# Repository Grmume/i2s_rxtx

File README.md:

# i2s_rxtx
Receiver and and (active) transmitter for I2S over ethernet cables.

Receiver for the 4 channels of digital audio (i2s) which can be transmitted using ethernet cables (>=Cat5).
Has a pin header to choose which channel is send to the i2s output, which can then be directed to an amp.
Contains an active transmitter to transmit all channels further to the next receiver.

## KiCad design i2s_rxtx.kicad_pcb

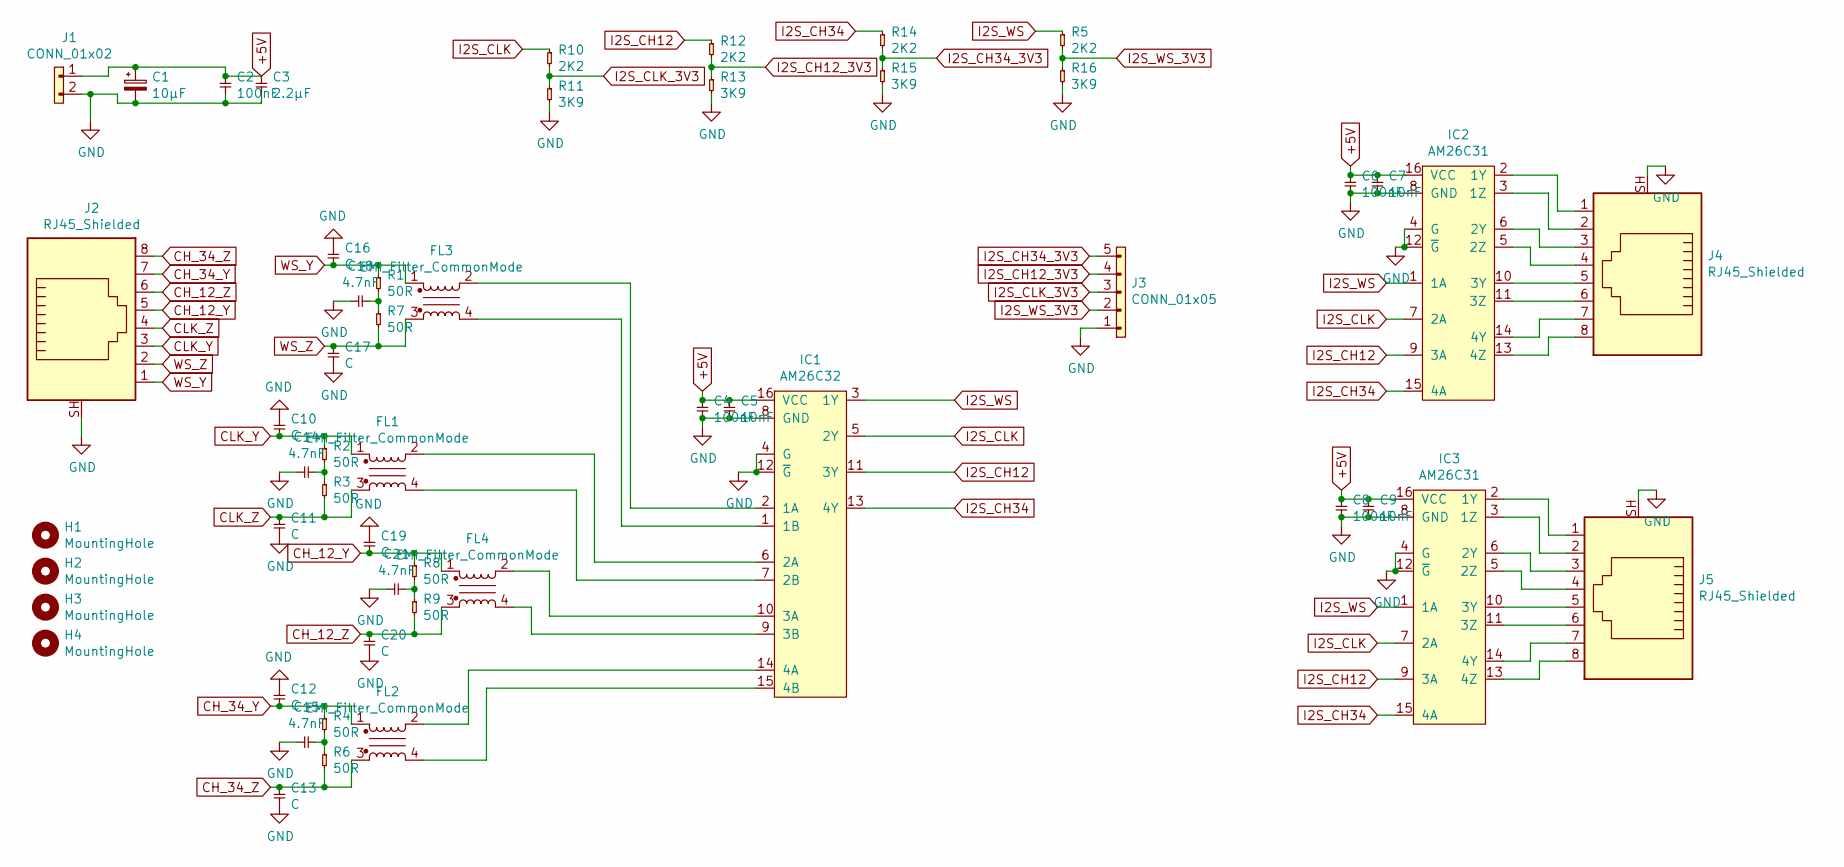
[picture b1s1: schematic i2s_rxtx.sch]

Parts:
C1: 10µF; CP_Elec_6.3x5.4
C2, C4, C6, C8: 100nF; C_0805_2012Metric_Pad1.15x1.40mm_HandSolder
C3: 2.2µF; C_0805_2012Metric_Pad1.15x1.40mm_HandSolder
C5, C7, C9: 10nF; C_0805_2012Metric_Pad1.15x1.40mm_HandSolder
C10, C11, C12, C13, C16, C17, C19, C20: C; C_0805_2012Metric_Pad1.15x1.40mm_HandSolder
C14, C15, C18, C21: 4.7nF; C_0805_2012Metric_Pad1.15x1.40mm_HandSolder
FL1, FL2, FL3, FL4: EMI_Filter_CommonMode; B82789_PinSwap
H1, H2, H3, H4: MountingHole; MountingHole_3.2mm_M3_Pad
IC1: AM26C32; SOIC-16; Farnell 1121592
IC2, IC3: AM26C31; SOIC-16; Farnell 4975637
J1: CONN_01x02; PinHeader_1x02_P2.00mm_Vertical
J2, J4, J5: RJ45_Shielded; RJ45_Weidmueller
J3: CONN_01x05; PinHeader_1x05_P2.00mm_Vertical
R1, R2, R3, R4, R6, R7, R8, R9: 50R; R_0805_2012Metric_Pad1.15x1.40mm_HandSolder
R5, R10, R12, R14: 2K2; R_0805_2012Metric_Pad1.15x1.40mm_HandSolder
R11, R13, R15, R16: 3K9; R_0805_2012Metric_Pad1.15x1.40mm_HandSolder

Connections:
+5V: C1.1, C2.1, C3.1, C4.1, C5.1, C6.1, C7.1, C8.1, C9.1, IC1.16 (VCC), IC2.16 (VCC), IC3.16 (VCC), J1.1
CH_12_Y: C19.2, FL4.1, J2.5, R8.1
CH_12_Z: C20.1, FL4.3, J2.6, R9.2
CH_34_Y: C12.2, FL2.1, J2.7, R4.1
CH_34_Z: C13.1, FL2.3, J2.8, R6.2
CLK_Y: C10.2, FL1.1, J2.3, R2.1
CLK_Z: C11.1, FL1.3, J2.4, R3.2
GND: C1.2, C2.2, C3.2, C4.2, C5.2, C6.2, C7.2, C8.2, C9.2, C10.1, C11.2, C12.1, C13.2, C14.1, C15.1, C16.1, C17.2, C18.1, C19.1, C20.2, C21.1, IC1.4 (G), IC1.8 (GND), IC1.12 (~G), IC2.4 (G), IC2.8 (GND), IC2.12 (~G), IC3.4 (G), IC3.8 (GND), IC3.12 (~G), J1.2, J2.SH, J3.1, J4.SH, J5.SH, R11.2, R13.2, R15.2, R16.2
I2S_CH12: IC1.11 (3Y), IC2.9 (3A), IC3.9 (3A), R12.1
I2S_CH12_3V3: J3.4, R12.2, R13.1
I2S_CH34: IC1.13 (4Y), IC2.15 (4A), IC3.15 (4A), R14.1
I2S_CH34_3V3: J3.5, R14.2, R15.1
I2S_CLK: IC1.5 (2Y), IC2.7 (2A), IC3.7 (2A), R10.1
I2S_CLK_3V3: J3.3, R10.2, R11.1
I2S_WS: IC1.3 (1Y), IC2.1 (1A), IC3.1 (1A), R5.1
I2S_WS_3V3: J3.2, R5.2, R16.1
unnamed: C14.2, R2.2, R3.1
unnamed: C15.2, R4.2, R6.1
unnamed: C18.2, R1.2, R7.1
unnamed: C21.2, R8.2, R9.1
unnamed: FL1.2, IC1.6 (2A)
unnamed: FL1.4, IC1.7 (2B)
unnamed: FL2.2, IC1.14 (4A)
unnamed: FL2.4, IC1.15 (4B)
unnamed: FL3.2, IC1.2 (1A)
unnamed: FL3.4, IC1.1 (1B)
unnamed: FL4.2, IC1.10 (3A)
unnamed: FL4.4, IC1.9 (3B)
unnamed: IC2.2 (1Y), J4.1
unnamed: IC2.3 (1Z), J4.2
unnamed: IC2.5 (2Z), J4.4
unnamed: IC2.6 (2Y), J4.3
unnamed: IC2.10 (3Y), J4.5
unnamed: IC2.11 (3Z), J4.6
unnamed: IC2.13 (4Z), J4.8
unnamed: IC2.14 (4Y), J4.7
unnamed: IC3.2 (1Y), J5.1
unnamed: IC3.3 (1Z), J5.2
unnamed: IC3.5 (2Z), J5.4
unnamed: IC3.6 (2Y), J5.3
unnamed: IC3.10 (3Y), J5.5
unnamed: IC3.11 (3Z), J5.6
unnamed: IC3.13 (4Z), J5.8
unnamed: IC3.14 (4Y), J5.7
WS_Y: C16.2, FL3.1, J2.1, R1.1
WS_Z: C17.1, FL3.3, J2.2, R7.2

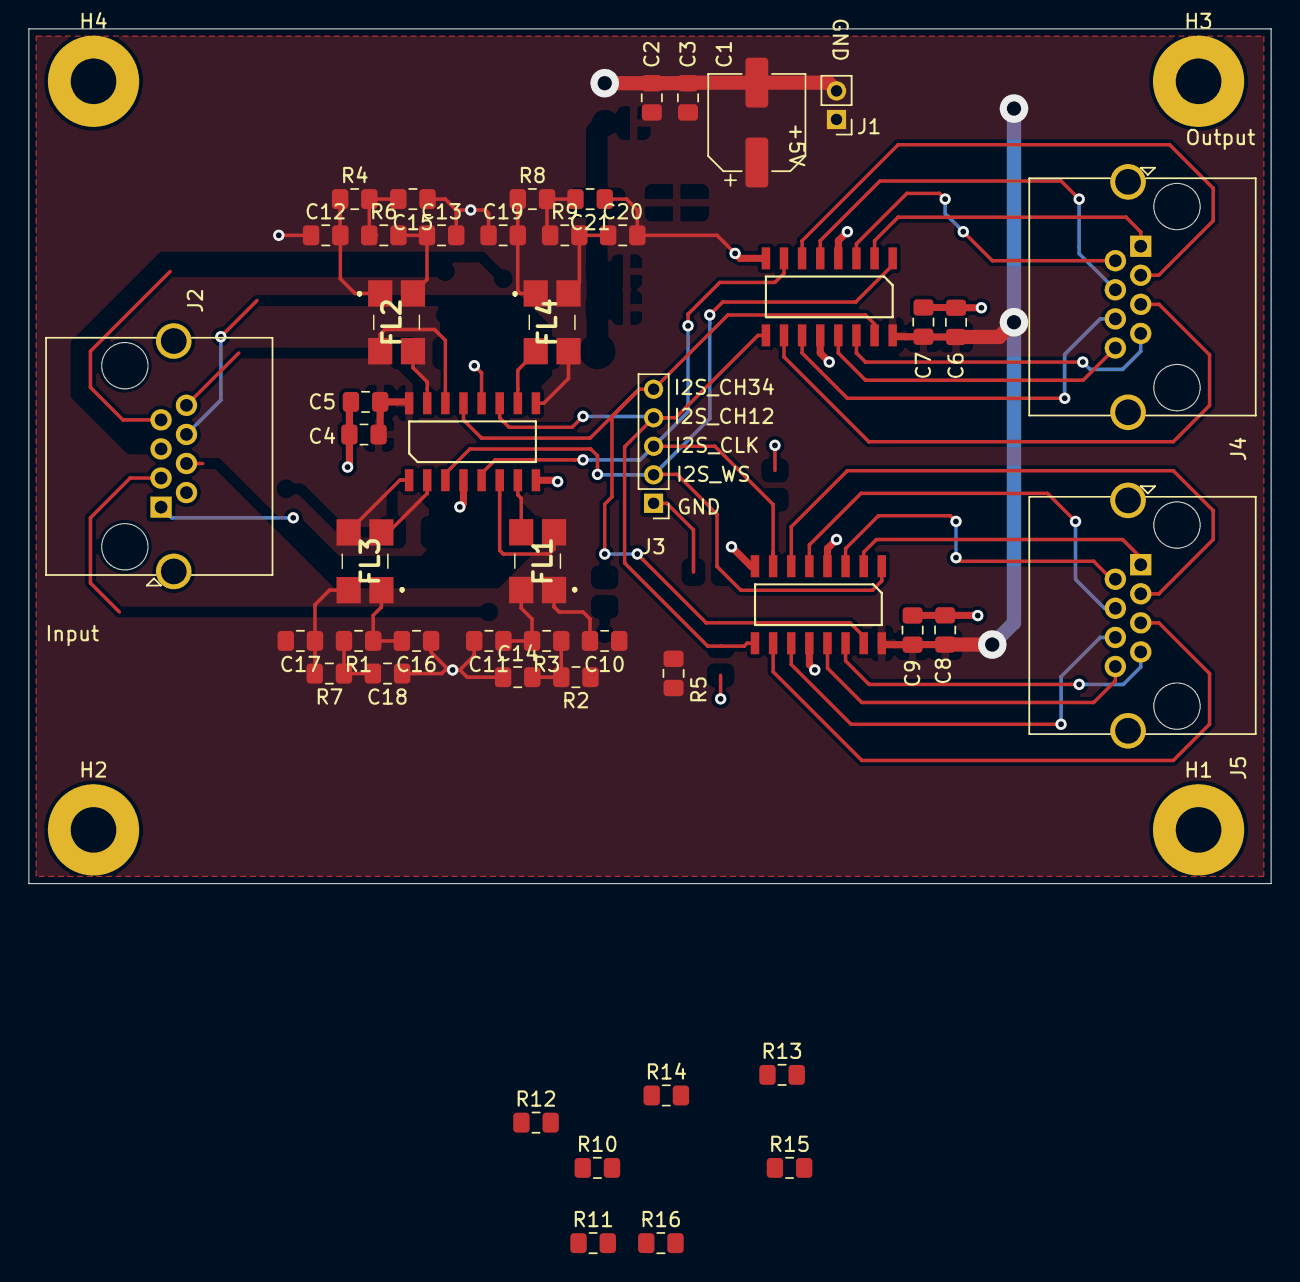
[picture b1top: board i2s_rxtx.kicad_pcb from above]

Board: 2 copper layers, 87.1 x 59.9 mm, 53 parts (0 on the bottom side), 46 nets.

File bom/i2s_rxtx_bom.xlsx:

Board | i2s_rxtx
BOM
References | Value | Footprint | Datasheet | Supplier1 Partnumber | Supplier2 Partnumber | Count | URL Reichelt | Unit Pr. Reichelt
C1 | 10µF | Capacitor_SMD:CP_Elec_6.3x5.4 | ~ |  |  | 1 | https://www.reichelt.de/smd-elko-10-f-50-v-85-c-2000-h-20-s-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 | 0.18
> C2, C4, C6, C8 | 100nF | Capacitor_SMD:C_0805_2012Metric_Pad1.15x1.40mm_HandSolder |  |  |  | 4
C3 | 2.2µF | Capacitor_SMD:C_0805_2012Metric_Pad1.15x1.40mm_HandSolder |  |  |  | 1
> C5, C7, C9 | 10nF | Capacitor_SMD:C_0805_2012Metric_Pad1.15x1.40mm_HandSolder |  |  |  | 3
> H1-H4 | MountingHole | MountingHole:MountingHole_3.2mm_M3_Pad | ~ |  |  | 4
IC1 | AM26C32 | agg:SOIC-16 | http://www.ti.com/lit/ds/symlink/am26c32.pdf | 1121592 | 595-AM26C32QDR | 1
> IC2, IC3 | AM26C31 | agg:SOIC-16 | http://www.ti.com.cn/cn/lit/ds/symlink/am26c31.pdf | 4975637 |  | 2
J1 | CONN_01x02 | Connector_PinHeader_2.00mm:PinHeader_1x02_P2.00mm_Vertical |  |  |  | 1
> J2, J4, J5 | RJ45_Shielded | agg:RJ45_Weidmueller | ~ |  |  | 3
J3 | CONN_01x05 | Connector_PinHeader_2.00mm:PinHeader_1x05_P2.00mm_Vertical |  |  |  | 1
> R1-R4 | 100R | Resistor_SMD:R_1206_3216Metric_Pad1.42x1.75mm_HandSolder |  |  |  | 4
> R5-R8 | 500K | Resistor_SMD:R_0805_2012Metric_Pad1.15x1.40mm_HandSolder |  |  |  | 4

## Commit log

2019-06-08 -- added receiver and transmitter
2019-06-15 -- update
2019-06-16 --update
2019-06-16 -- updated gerbers
2019-06-16 -- changed vias
2019-06-16 -- added mounting holes
2019-06-16 -- update gerbers zip
2019-07-19 -- added bom
2019-08-14 -- added voltage divider for 3.3V outputs
2019-08-16 -- updated termination network replaced termination resistor by a split termination added common mode chokes added capacitors
2019-08-17 -- added capacitors to data lines
    -- added spreadsheet to calculate capacitor values based on sample rate
2019-08-25 adjusted pcb layout to new termination network
